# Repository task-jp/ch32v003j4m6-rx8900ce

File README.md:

# Gathering CLOCK

Simple two LEDs clock that tells first 5mins in hours.

## Features

|Min  |Green|Red  |
|-----|-----|-----|
|00-05|On   |     |
|05-10|     |Blink|
|10-55|     |On   |
|55-60|Blink|     |

* pushing a button for over 30 secs resets the clock

## Schematic and Layout

## Bill Of Materials

|Ref     |Name          |Qty|Description     |Link                                        |
|--------|--------------|  -|----------------|--------------------------------------------|
|U1      |CH32V003J4M6  |  1|Micro Controller|https://akizukidenshi.com/catalog/g/g118062/|
|U2      |RX8900CE      |  1|RTC             |https://akizukidenshi.com/catalog/g/g113320/|
|BT1     |Battery holder|  1|CR1220          |https://akizukidenshi.com/catalog/g/g109561/|
|D1      |LED           |  1|Green           |https://akizukidenshi.com/catalog/g/g106417/|
|D2      |LED           |  1|Red             |https://akizukidenshi.com/catalog/g/g103978/|
|C1,C2,C3|Capacitor     |  3|0.1uF           |https://akizukidenshi.com/catalog/g/g113374/|
|R1,R2   |Resistor 200  |  2|LED limit       |https://akizukidenshi.com/catalog/g/g106201/|
|R3,R4   |Resistor 3K3  |  2|Pull up         |https://akizukidenshi.com/catalog/g/g114661/|
|SW1     |Push Switch   |  1|                |https://akizukidenshi.com/catalog/g/g115969/|

## Case

- [Fusion f3d file](./fusion/ch32v003j4m6-rx8900.f3d)
- STL
  - [Front](fusion/ch32v003j4m6-case-front.stl)
  - [Back](fusion/ch32v003j4m6-case-back.stl)

## License
* MIT

## Author
* stasuku@gmail.com

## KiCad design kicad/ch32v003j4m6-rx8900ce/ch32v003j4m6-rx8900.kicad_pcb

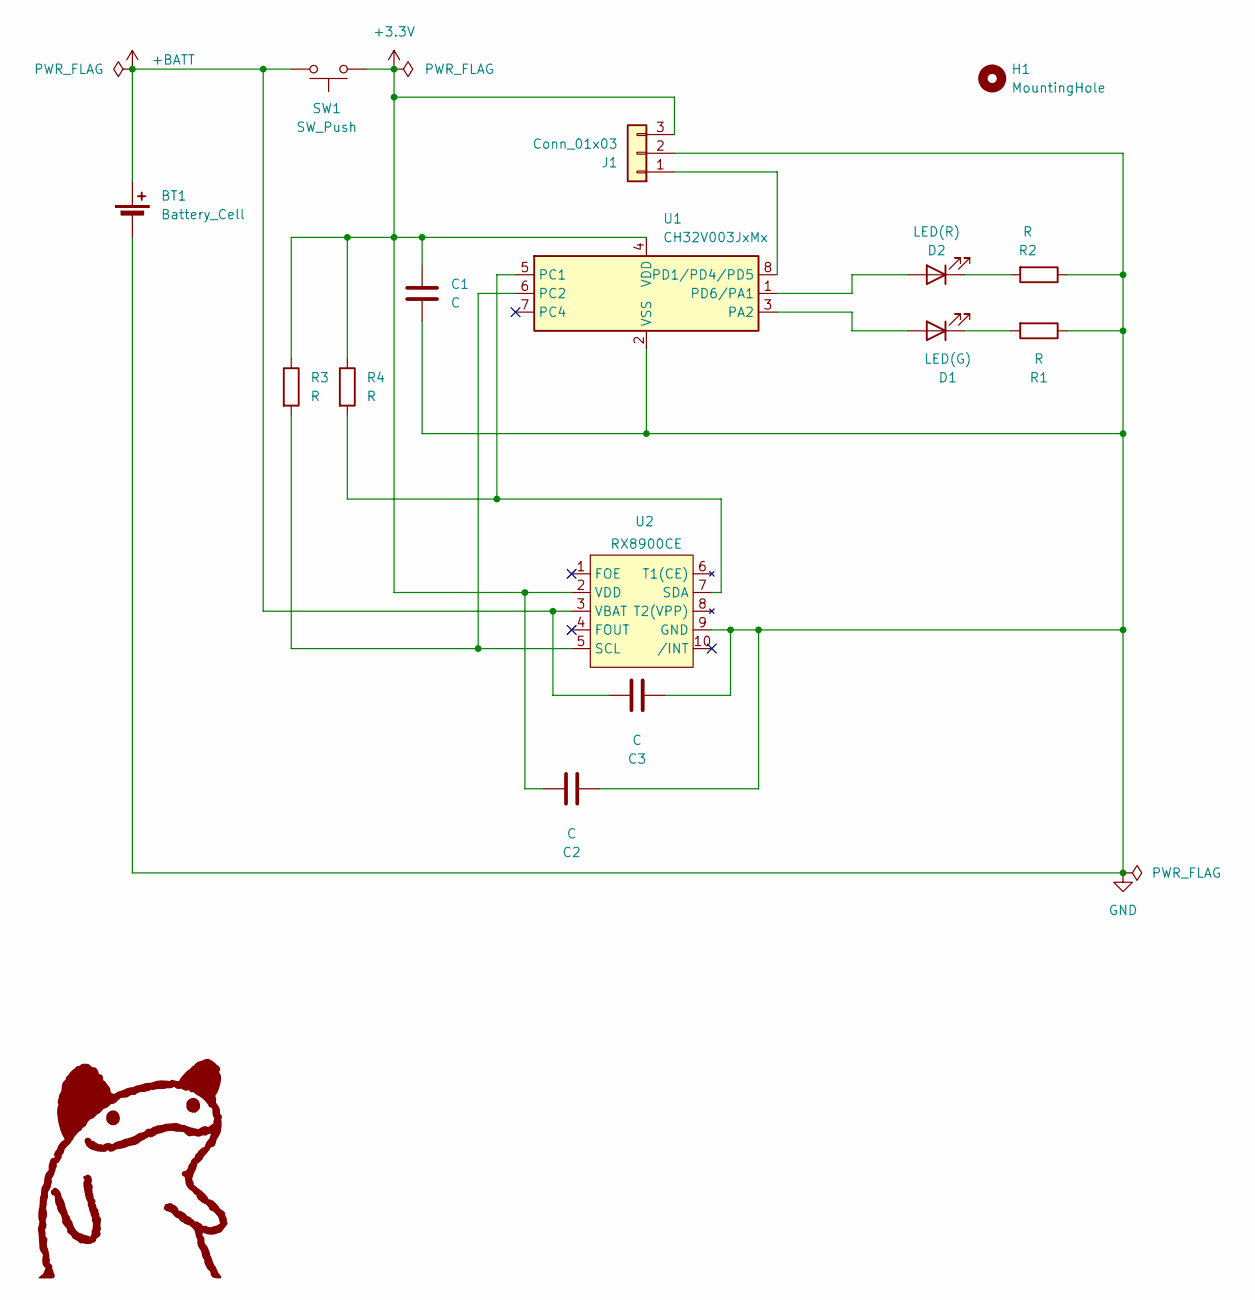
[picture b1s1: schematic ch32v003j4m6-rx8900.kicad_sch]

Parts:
BT1: Battery_Cell; CH291-1220LF
C1, C2, C3: C; C_0603_1608Metric
D1: LED(G); LED_0603_1608Metric
D2: LED(R); LED_0603_1608Metric
H1: MountingHole; MountingHole_3mm
J1: Conn_01x03; PinSocket_1x03_P2.54mm_Horizontal
R1, R2, R3, R4: R; R_0603_1608Metric
SW1: SW_Push; SW_Push_1P1T_NO_6x6mm_H9.5mm
U1: CH32V003JxMx; SOP-8_3.9x4.9mm_P1.27mm
U2: RX8900CE; EPSON_CE-USON-10_USON-10_3.2x2.5mm_P0.7mm

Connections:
+3.3V: C1.2, C2.2, J1.3, R3.1, R4.1, SW1.1, U1.4 (VDD), U2.2 (VDD)
+BATT: BT1.1 (+), C3.2, SW1.2, U2.3 (VBAT)
GND: BT1.2 (-), C1.1, C2.1, C3.1, J1.2, R1.1, R2.1, U1.2 (VSS), U2.9 (GND)
unnamed: D1.2 (A), U1.3 (PA2)
unnamed: D1.1 (K), R1.2
unnamed: D2.2 (A), U1.1 (PD6/PA1)
unnamed: D2.1 (K), R2.2
unnamed: J1.1, U1.8 (PD1/PD4/PD5)
unnamed: R4.2, U1.5 (PC1), U2.7 (SDA)
unnamed: R3.2, U1.6 (PC2), U2.5 (SCL)

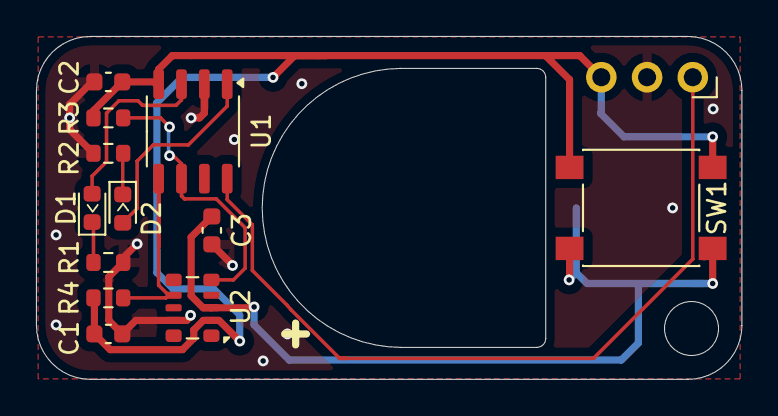
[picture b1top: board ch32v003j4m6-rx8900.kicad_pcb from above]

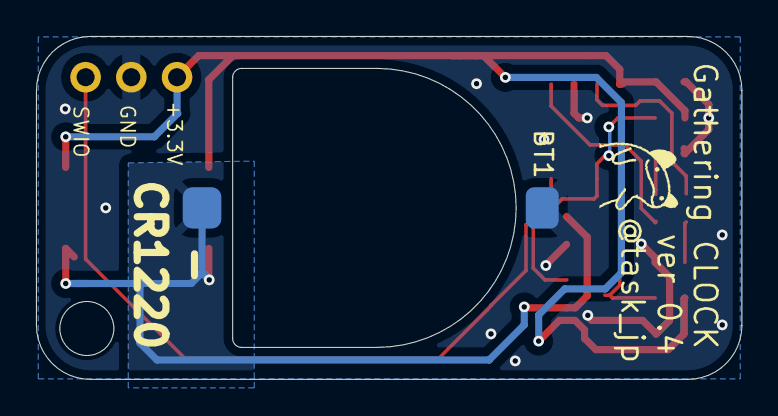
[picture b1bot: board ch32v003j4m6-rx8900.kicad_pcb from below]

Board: 2 copper layers, 39.2 x 19.0 mm, 15 parts (2 on the bottom side), 10 nets.

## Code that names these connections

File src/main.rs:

#![no_std]
#![no_main]

use ch32v00x_hal as hal;
use ch32v_rt::entry;
use chrono::NaiveDateTime;
use hal::{i2c::*, pac::Peripherals, prelude::*};
use rx8900::Rx8900;
use fugit::HertzU32 as Hertz;
use embedded_hal::blocking::delay::DelayMs;
use hal::println;

#[panic_handler]
fn panic(info: &core::panic::PanicInfo) -> ! {
    println!("{}", info);
    loop {}
}

struct Ch32Delay {
    sysclock: Hertz,
}

impl Ch32Delay {
    fn new(sysclock: Hertz) -> Self {
        Self { sysclock }
    }
}

impl DelayMs<u32> for Ch32Delay
{
    fn delay_ms(&mut self, ms: u32) {
        let cycles = self.sysclock.raw() / 1000 * ms / 2;
        unsafe {
            qingke::riscv::asm::delay(cycles);
        }
    }
}

#[entry]
fn main() -> ! {
    #[cfg(feature = "sdi_print")]
    hal::debug::SDIPrint::enable();

    let pac = Peripherals::take().unwrap();

    let mut rcc = pac.RCC.constrain();
    let clocks = rcc.config.freeze();

    let gpioa = pac.GPIOA.split(&mut rcc);
    #[cfg(feature = "rtc")]
    let gpioc = pac.GPIOC.split(&mut rcc);
    let mut red = gpioa.pa1.into_push_pull_output();
    let mut green = gpioa.pa2.into_push_pull_output();
    #[cfg(feature = "rtc")]
    let sda = gpioc.pc1.into_alternate_open_drain();
    #[cfg(feature = "rtc")]
    let scl = gpioc.pc2.into_alternate_open_drain();
    #[cfg(feature = "rtc")]
    let i2c = I2c::i2c1(
        pac.I2C1,
        scl,
        sda,
        I2cConfig::fast_mode(),
        &mut rcc,
        &clocks,
    );

    let mut delay = Ch32Delay::new(clocks.sysclk());

    #[cfg(feature = "rtc")]
    let mut rx8900 = Rx8900::new(i2c);

    #[cfg(feature = "rtc")]
    match rx8900.voltage_low_flag() {
        Ok(true) => {
            #[cfg(feature = "sdi_print")]
            println!("Voltage low flag is set");
            rx8900.init().unwrap();
            delay.delay_ms(10u32);
            rx8900.set_datetime(NaiveDateTime::new(
                chrono::NaiveDate::from_ymd_opt(2024, 1, 1).unwrap(),
                chrono::NaiveTime::from_hms_opt(0, 0, 0).unwrap(),
            )).unwrap();
        },
        #[cfg(feature = "sdi_print")]
        Ok(false) => {
            println!("Voltage low flag is not set");
        },
        #[cfg(feature = "sdi_print")]
        Err(e) => {
            println!("Error occured: {:?}", e);
        },
        _ => {}
    }

    #[cfg(feature = "rtc")]
    let mut counter: usize = 0;
    #[cfg(feature = "rtc")]
    let mut last_second: u8 = core::u8::MAX;

    loop {
        #[cfg(feature = "rtc")]
        {
            let second = rx8900.sec().unwrap();
            if second == last_second {
                delay.delay_ms(10u32);
                continue;
            }

            if counter < 20 {
                counter += 1;
            } else if counter < 30 {
                counter += 1;
                green.set_low();
                red.set_high();
                delay.delay_ms(500);
                green.set_high();
                red.set_low();
                delay.delay_ms(400);
                continue;
            } else {
                green.set_high();
                red.set_high();
                rx8900.set_datetime(NaiveDateTime::new(
                    chrono::NaiveDate::from_ymd_opt(2024, 1, 1).unwrap(),
                    chrono::NaiveTime::from_hms_opt(0, 0, 0).unwrap(),
                )).unwrap();
                continue;
            }

            last_second = second;

            let minutes = rx8900.min().unwrap();
            #[cfg(feature = "sdi_print")]
            println!("{:02}:{:02}", minutes, second);

            match minutes {
                55..=59 => {
                    // 待ち合わせ時間直前5分間は緑を点滅
                    red.set_low();
                    green.set_high();
                    delay.delay_ms(500);
                    green.set_low();
                    delay.delay_ms(400);
                },
                0..=4 => {
                    // 5分間の待ち合わせ時間内は緑を点灯
                    green.set_high();
                    red.set_low();
                    delay.delay_ms(900);
                },
                5..=9 => {
                    // 待ち合わせ時間が過ぎたら5分間赤を点滅
                    red.set_high();
                    green.set_low();
                    delay.delay_ms(500);
                    red.set_low();
                    delay.delay_ms(400);
                },
                _ => {
                    // それ以外の場合は赤を点灯
                    green.set_low();
                    red.set_high();
                    delay.delay_ms(900);
                }
            }
        }

        #[cfg(not(feature = "rtc"))]
        {
            green.set_high();
            red.set_high();
            delay.delay_ms(500);
            green.set_low();
            delay.delay_ms(400);
        }
    }
}

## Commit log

2024-01-15 Use ch32v00x_hal
2024-03-20 Impl functionalities
2024-03-20 Add kicad files
2024-03-20 Keep reseting while button pressed over 60 secs
2024-03-20 Remove hour which is not used
2024-03-20 Fix indentation
2024-03-20 Do not handle vlf != true when debug print is disabled
2024-03-20 Remove a variable
2024-03-20 header cleanup
2024-03-21 Update kicad files
2024-03-21 Improve reset sequence
2024-04-12 Update pcb/sch
2024-04-12 Swap blink color befor/after the term
2024-04-12 Add README
2024-04-12 Add resources for README
2024-04-12 Add case data
2024-04-13 Update case
2024-04-15 Fix suffix of gif animation
2024-04-15 Fix suffix of case in README
2024-04-15 Update front cover
2024-04-16 Use public crate for RX8900
2024-04-17 Fix project name
2024-05-17 Update front case
